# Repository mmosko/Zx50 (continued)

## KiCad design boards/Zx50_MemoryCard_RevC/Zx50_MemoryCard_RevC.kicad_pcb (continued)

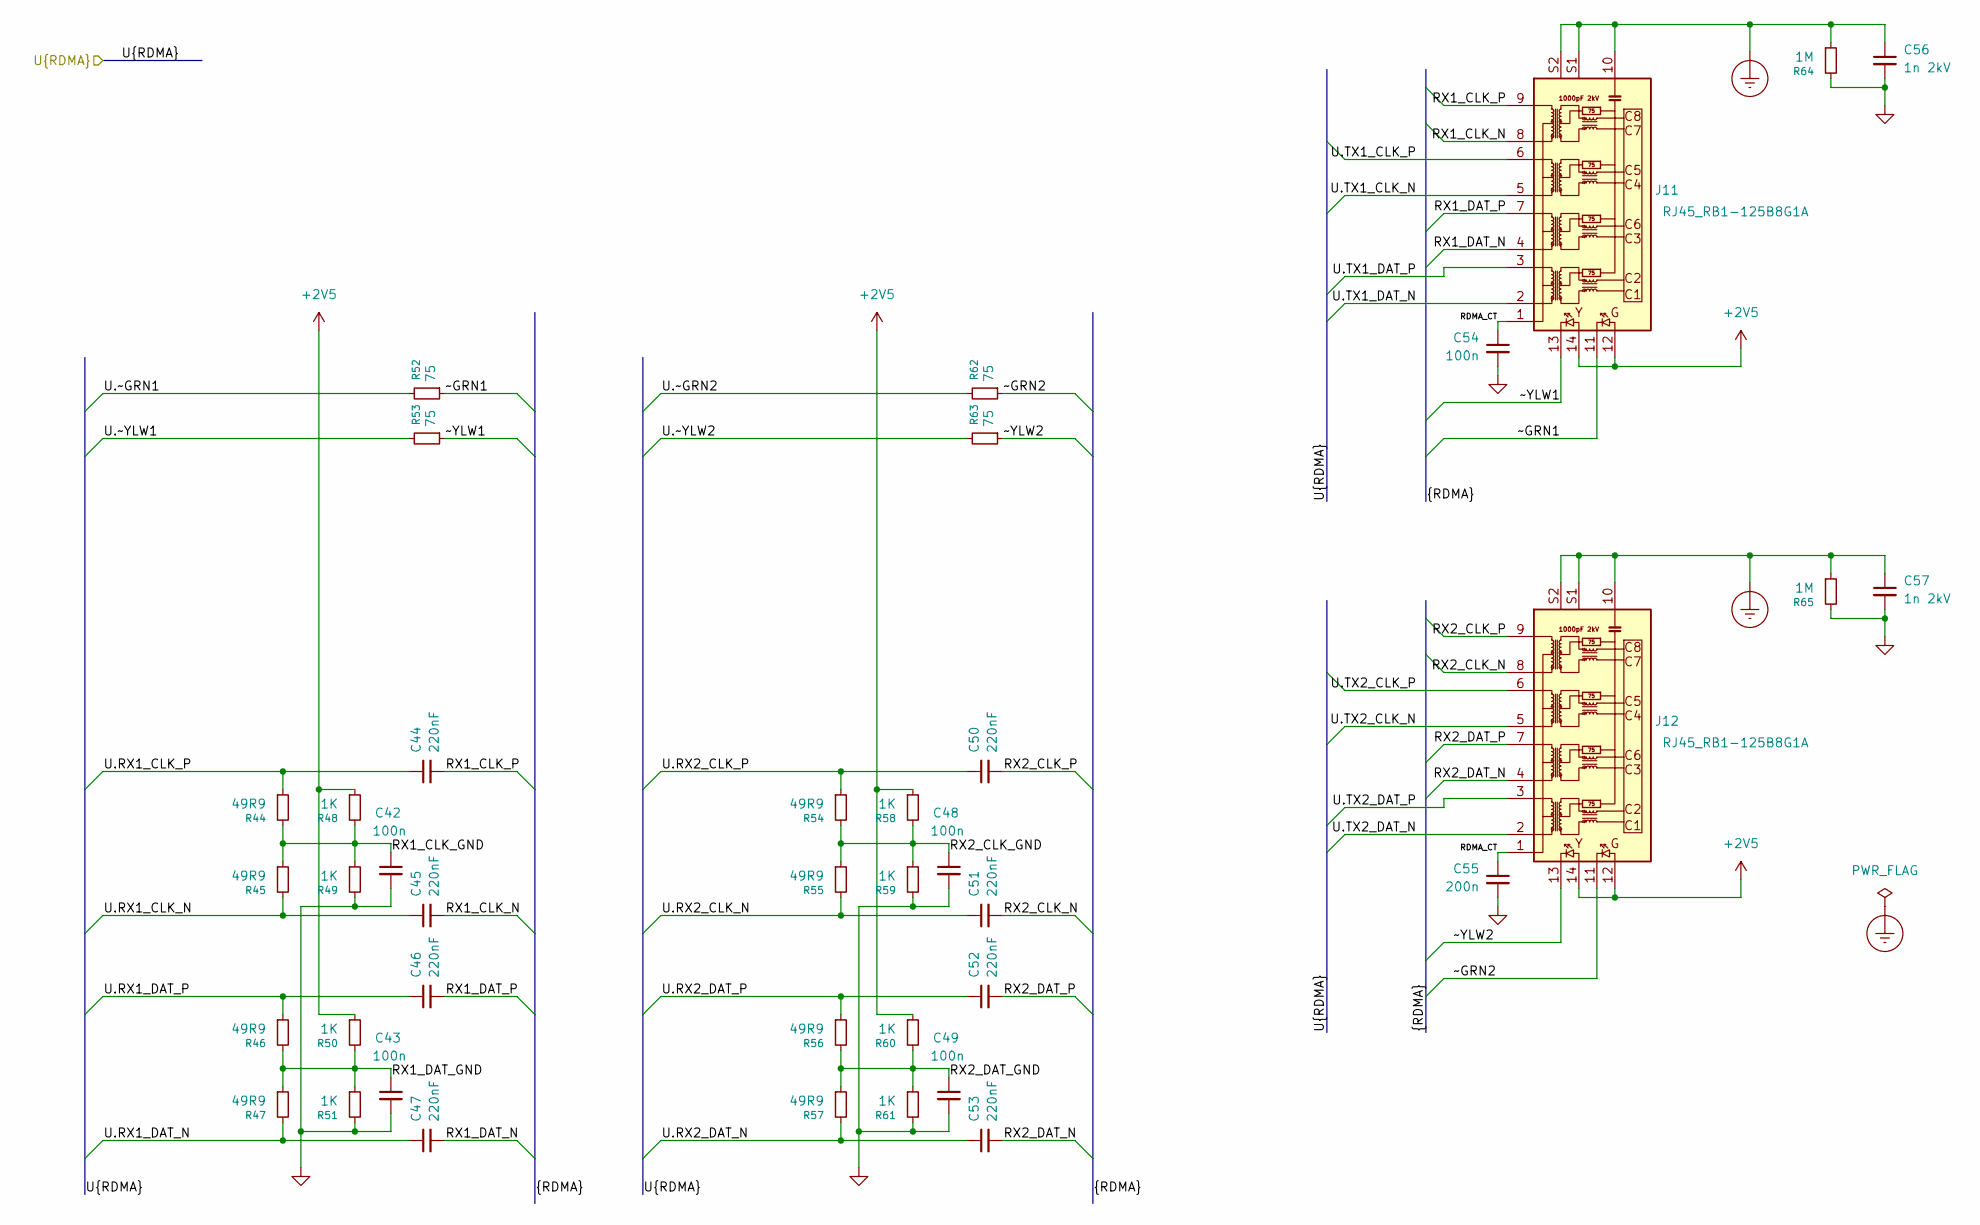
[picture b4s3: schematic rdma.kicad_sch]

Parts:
C42, C43, C48, C49, C54: 100n; C_0402_1005Metric; LCSC C1525
C44, C45, C46, C47, C50, C51, C52, C53: 220nF; C_0402_1005Metric; LCSC C16772
C55: 200n; C_0402_1005Metric; LCSC C1525
C56, C57: 1n 2kV; C_1206_3216Metric; LCSC C9196
J11, J12: RJ45_RB1-125B8G1A; HANRUN_HR911130A; MFG_PN HR911130C; LCSC C50933
R44, R45, R46, R47, R54, R55, R56, R57: 49R9; R_0402_1005Metric; MFG_PN 0402WGF499JTCE; LCSC C25120
R48, R49, R50, R51, R58, R59, R60, R61: 1K; R_0402_1005Metric; MFG_PN 0402WGF1001TCE; LCSC C11702
R52, R53, R62, R63: 75; R_0603_1608Metric; MFG_PN 0603WAF750JT5E; LCSC C4275
R64, R65: 1M; R_0805_2012Metric; MFG_PN 0805W8F1004T5E; LCSC C17514

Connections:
+2V5: J11.12, J11.14, J12.12, J12.14, R48.1, R50.1, R58.1, R60.1; also elsewhere on the board
/FPGA/RDMA/RDMA_CT: C54.1, C55.1, J11.1 (CT), J12.1 (CT)
/FPGA/RDMA/RX1_CLK_GND: C42.1, R44.2, R45.1, R48.2, R49.1
/FPGA/RDMA/RX1_CLK_N: C45.2, J11.8 (TD4+)
/FPGA/RDMA/RX1_CLK_P: C44.2, J11.9 (TD4-)
/FPGA/RDMA/RX1_DAT_GND: C43.1, R46.2, R47.1, R50.2, R51.1
/FPGA/RDMA/RX1_DAT_N: C47.2, J11.4 (TD2+)
/FPGA/RDMA/RX1_DAT_P: C46.2, J11.7 (TD2-)
/FPGA/RDMA/RX2_CLK_GND: C48.1, R54.2, R55.1, R58.2, R59.1
/FPGA/RDMA/RX2_CLK_N: C51.2, J12.8 (TD4+)
/FPGA/RDMA/RX2_CLK_P: C50.2, J12.9 (TD4-)
/FPGA/RDMA/RX2_DAT_GND: C49.1, R56.2, R57.1, R60.2, R61.1
/FPGA/RDMA/RX2_DAT_N: C53.2, J12.4 (TD2+)
/FPGA/RDMA/RX2_DAT_P: C52.2, J12.7 (TD2-)
/FPGA/RDMA/~GRN1: J11.11, R52.1
/FPGA/RDMA/~GRN2: J12.11, R62.1
/FPGA/RDMA/~YLW1: J11.13, R53.1
/FPGA/RDMA/~YLW2: J12.13, R63.1
/FPGA/U.RX1_CLK_N: C45.1, R45.2; also elsewhere on the board
/FPGA/U.RX1_CLK_P: C44.1, R44.1; also elsewhere on the board
/FPGA/U.RX1_DAT_N: C47.1, R47.2; also elsewhere on the board
/FPGA/U.RX1_DAT_P: C46.1, R46.1; also elsewhere on the board
/FPGA/U.RX2_CLK_N: C51.1, R55.2; also elsewhere on the board
/FPGA/U.RX2_CLK_P: C50.1, R54.1; also elsewhere on the board
/FPGA/U.RX2_DAT_N: C53.1, R57.2; also elsewhere on the board
/FPGA/U.RX2_DAT_P: C52.1, R56.1; also elsewhere on the board
/FPGA/U.TX1_CLK_N: J11.5 (TD3+); also elsewhere on the board
/FPGA/U.TX1_CLK_P: J11.6 (TD3-); also elsewhere on the board
/FPGA/U.TX1_DAT_N: J11.2 (TD1+); also elsewhere on the board
/FPGA/U.TX1_DAT_P: J11.3 (TD1-); also elsewhere on the board
/FPGA/U.TX2_CLK_N: J12.5 (TD3+); also elsewhere on the board
/FPGA/U.TX2_CLK_P: J12.6 (TD3-); also elsewhere on the board
/FPGA/U.TX2_DAT_N: J12.2 (TD1+); also elsewhere on the board
/FPGA/U.TX2_DAT_P: J12.3 (TD1-); also elsewhere on the board
/FPGA/U.~GRN1: R52.2; also elsewhere on the board
/FPGA/U.~GRN2: R62.2; also elsewhere on the board
/FPGA/U.~YLW1: R53.2; also elsewhere on the board
/FPGA/U.~YLW2: R63.2; also elsewhere on the board
Earth_Protective: C56.1, C57.1, J11.10 (GND), J11.S1, J11.S2, J12.10 (GND), J12.S1, J12.S2, R64.1, R65.1
GND: C42.2, C43.2, C48.2, C49.2, C54.2, C55.2, C56.2, C57.2, R49.2, R51.2, R59.2, R61.2, R64.2, R65.2; also elsewhere on the board

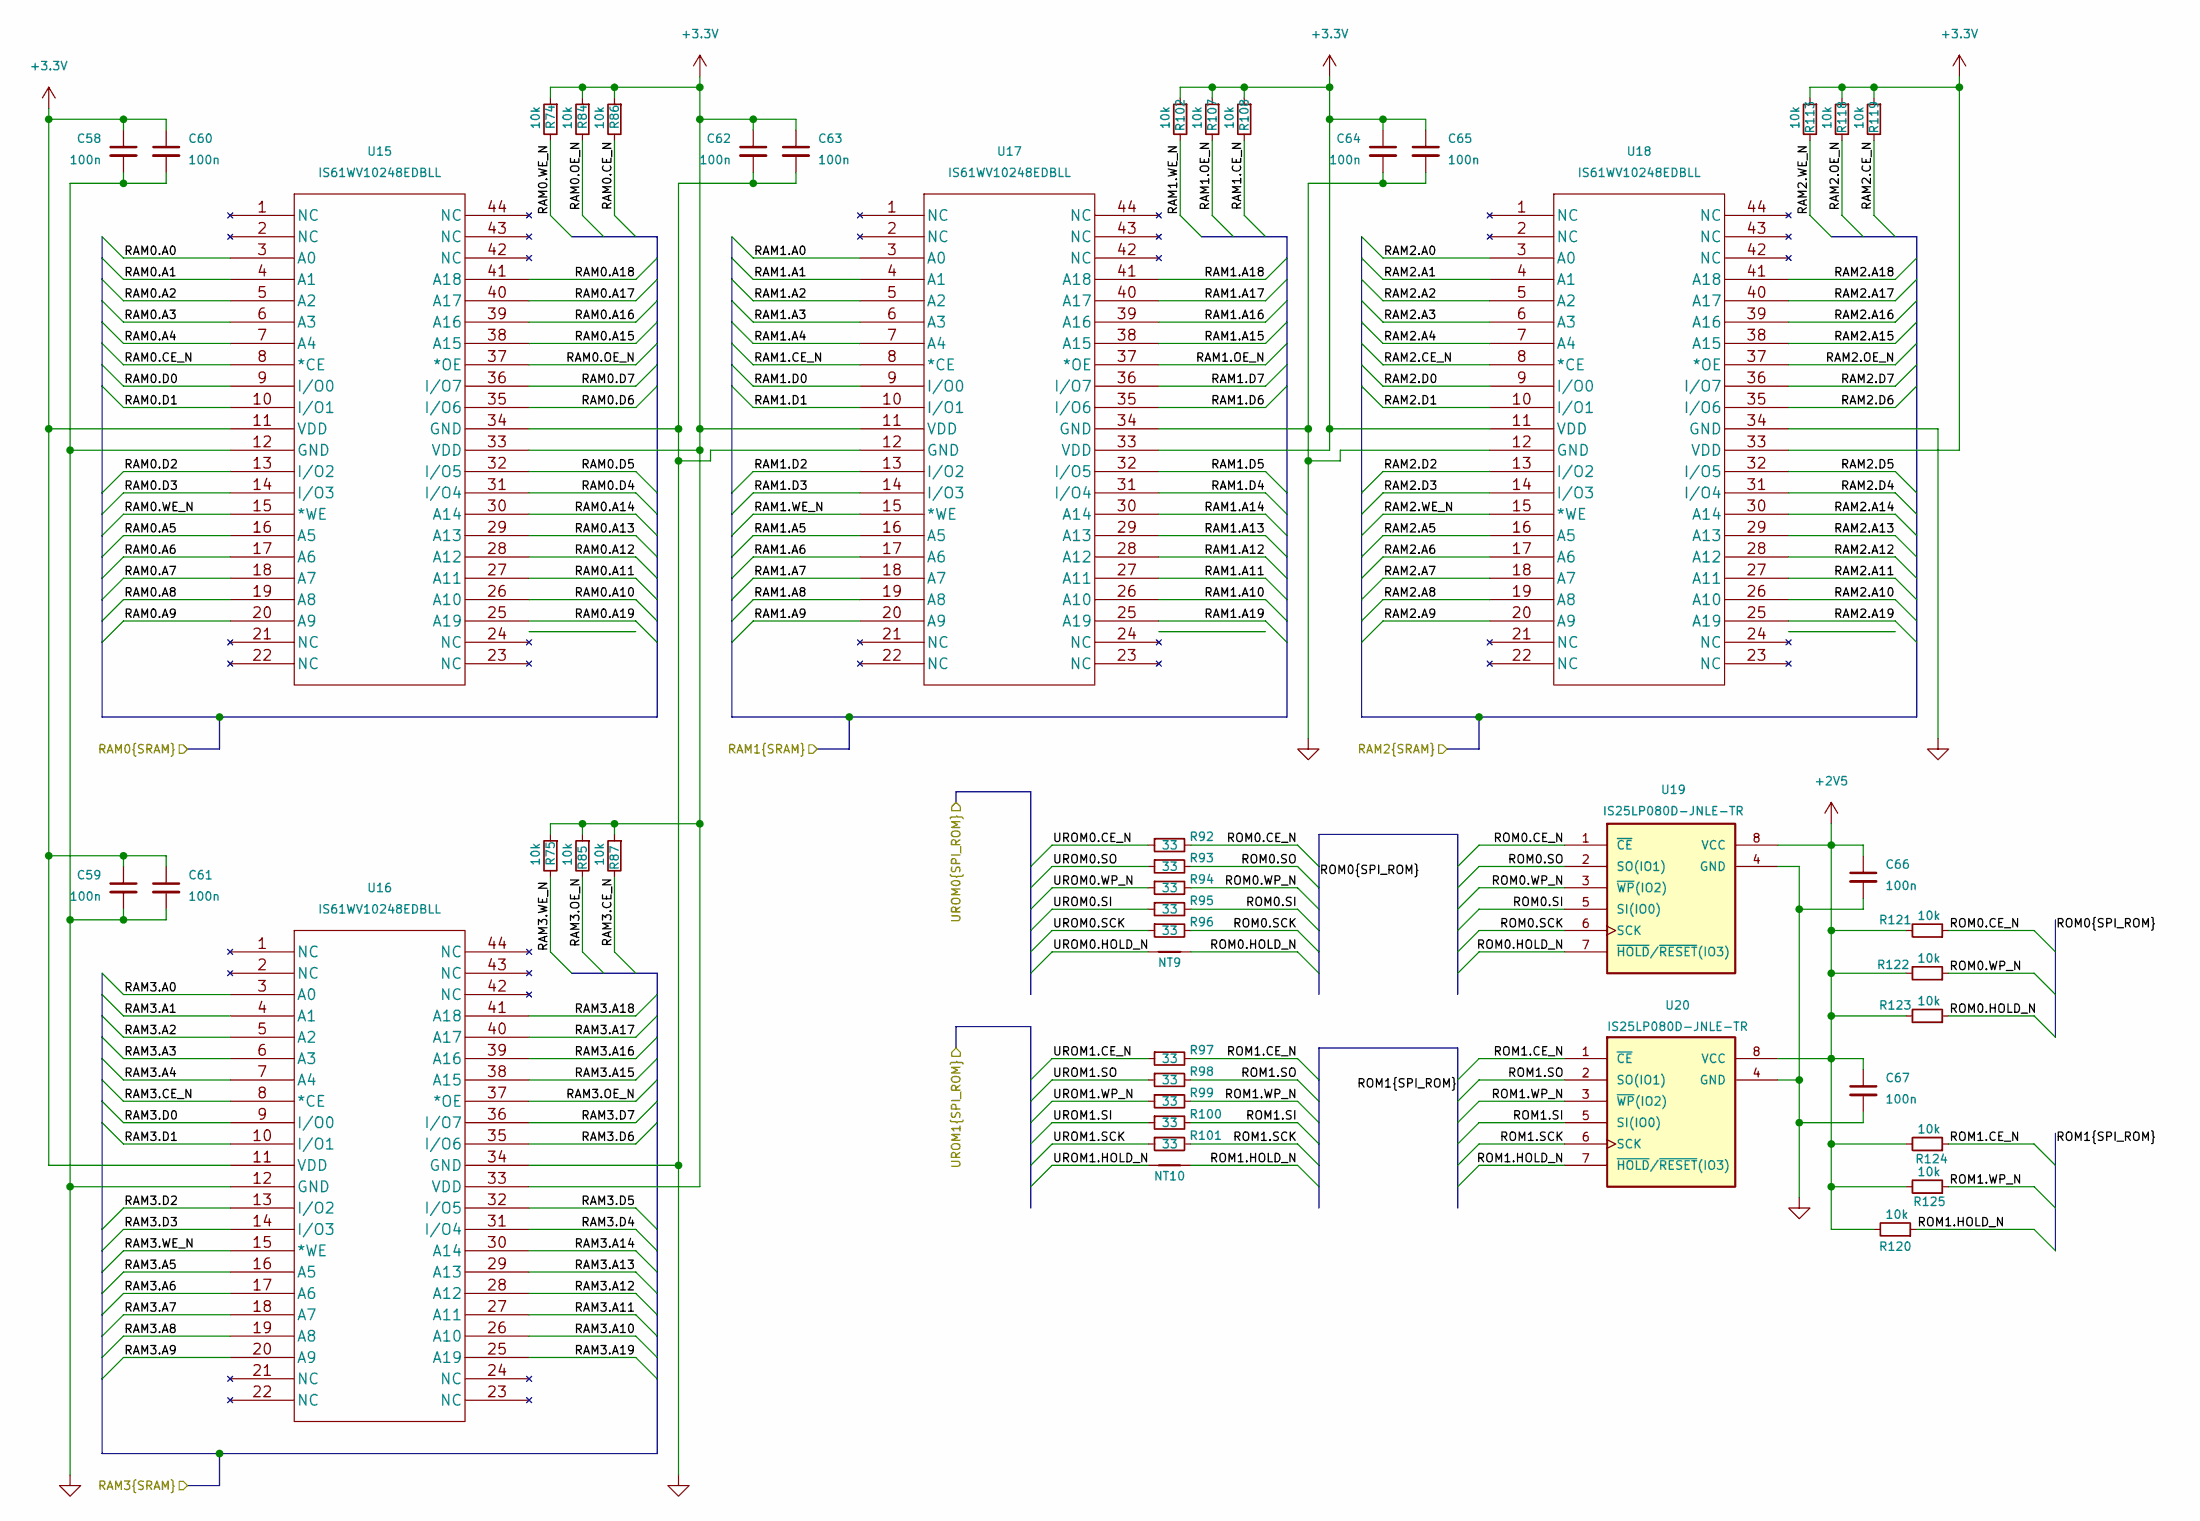
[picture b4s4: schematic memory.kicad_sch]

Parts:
C58, C59, C60, C61, C62, C63, C64, C65, C66, C67: 100n; C_0402_1005Metric; LCSC C1525
NT9, NT10: NetTie_2
R74, R75, R84, R85, R86, R87, R102, R107, R108, R113, R118, R119, R120, R121, R122, R123, R124, R125: 10k; R_0402_1005Metric; MFG_PN 0402WGF1002TCE; LCSC C25744
R92, R93, R94, R95, R96, R97, R98, R99, R100, R101: 33; R_0402_1005Metric; MFG_PN 0402WGF1000TCE; LCSC C25076
U15, U16, U17, U18: IS61WV10248EDBLL; TSOP-44_11P9X18P5_ISI; LCSC C1349228
U19, U20: IS25LP080D-JNLE-TR; SOIC127P600X88-8N; DigiKey_PN 706-1581-1-ND

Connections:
+2V5: C66.1, C67.1, R120.2, R121.2, R122.2, R123.2, R124.2, R125.2, U19.8 (VCC), U20.8 (VCC); also elsewhere on the board
+3.3V: C58.1, C59.1, C60.1, C61.1, C62.1, C63.1, C64.1, C65.1, R74.1, R75.1, R84.1, R85.1, R86.1, R87.1, R102.1, R107.1, R108.1, R113.1, R118.1, R119.1, U15.11 (VDD), U15.33 (VDD), U16.11 (VDD), U16.33 (VDD), U17.11 (VDD), U17.33 (VDD), U18.11 (VDD), U18.33 (VDD); also elsewhere on the board
/FPGA/RAM0.A0: U15.3 (A0)
/FPGA/RAM0.A1: U15.4 (A1)
/FPGA/RAM0.A2: U15.5 (A2)
/FPGA/RAM0.A3: U15.6 (A3)
/FPGA/RAM0.A4: U15.7 (A4)
/FPGA/RAM0.A5: U15.16 (A5)
/FPGA/RAM0.A6: U15.17 (A6)
/FPGA/RAM0.A7: U15.18 (A7)
/FPGA/RAM0.A8: U15.19 (A8)
/FPGA/RAM0.A9: U15.20 (A9)
/FPGA/RAM0.A10: U15.26 (A10)
/FPGA/RAM0.A11: U15.27 (A11)
/FPGA/RAM0.A12: U15.28 (A12)
/FPGA/RAM0.A13: U15.29 (A13)
/FPGA/RAM0.A14: U15.30 (A14)
/FPGA/RAM0.A15: U15.38 (A15)
/FPGA/RAM0.A16: U15.39 (A16)
/FPGA/RAM0.A17: U15.40 (A17)
/FPGA/RAM0.A18: U15.41 (A18)
/FPGA/RAM0.A19: U15.25 (A19)
/FPGA/RAM0.CE_N: R86.2, U15.8 (*CE)
/FPGA/RAM0.D0: U15.9 (I/O0)
/FPGA/RAM0.D1: U15.10 (I/O1)
/FPGA/RAM0.D2: U15.13 (I/O2)
/FPGA/RAM0.D3: U15.14 (I/O3)
/FPGA/RAM0.D4: U15.31 (I/O4)
/FPGA/RAM0.D5: U15.32 (I/O5)
/FPGA/RAM0.D6: U15.35 (I/O6)
/FPGA/RAM0.D7: U15.36 (I/O7)
/FPGA/RAM0.OE_N: R84.2, U15.37 (*OE)
/FPGA/RAM0.WE_N: R74.2, U15.15 (*WE)
/FPGA/RAM1.A0: U17.3 (A0); also elsewhere on the board
/FPGA/RAM1.A1: U17.4 (A1); also elsewhere on the board
/FPGA/RAM1.A2: U17.5 (A2); also elsewhere on the board
/FPGA/RAM1.A3: U17.6 (A3); also elsewhere on the board
/FPGA/RAM1.A4: U17.7 (A4); also elsewhere on the board
/FPGA/RAM1.A5: U17.16 (A5); also elsewhere on the board
/FPGA/RAM1.A6: U17.17 (A6); also elsewhere on the board
/FPGA/RAM1.A7: U17.18 (A7); also elsewhere on the board
/FPGA/RAM1.A8: U17.19 (A8); also elsewhere on the board
/FPGA/RAM1.A9: U17.20 (A9); also elsewhere on the board
/FPGA/RAM1.A10: U17.26 (A10); also elsewhere on the board
/FPGA/RAM1.A11: U17.27 (A11); also elsewhere on the board
/FPGA/RAM1.A12: U17.28 (A12); also elsewhere on the board
/FPGA/RAM1.A13: U17.29 (A13); also elsewhere on the board
/FPGA/RAM1.A14: U17.30 (A14); also elsewhere on the board
/FPGA/RAM1.A15: U17.38 (A15); also elsewhere on the board
/FPGA/RAM1.A16: U17.39 (A16); also elsewhere on the board
/FPGA/RAM1.A17: U17.40 (A17); also elsewhere on the board
/FPGA/RAM1.A18: U17.41 (A18); also elsewhere on the board
/FPGA/RAM1.A19: U17.25 (A19); also elsewhere on the board
/FPGA/RAM1.CE_N: R108.2, U17.8 (*CE); also elsewhere on the board
/FPGA/RAM1.D0: U17.9 (I/O0); also elsewhere on the board
/FPGA/RAM1.D1: U17.10 (I/O1); also elsewhere on the board
/FPGA/RAM1.D2: U17.13 (I/O2); also elsewhere on the board
/FPGA/RAM1.D3: U17.14 (I/O3); also elsewhere on the board
/FPGA/RAM1.D4: U17.31 (I/O4); also elsewhere on the board
/FPGA/RAM1.D5: U17.32 (I/O5); also elsewhere on the board
/FPGA/RAM1.D6: U17.35 (I/O6); also elsewhere on the board
/FPGA/RAM1.D7: U17.36 (I/O7); also elsewhere on the board
/FPGA/RAM1.OE_N: R107.2, U17.37 (*OE); also elsewhere on the board
/FPGA/RAM1.WE_N: R102.2, U17.15 (*WE); also elsewhere on the board
/FPGA/RAM2.A0: U18.3 (A0)
/FPGA/RAM2.A1: U18.4 (A1)
/FPGA/RAM2.A2: U18.5 (A2)
/FPGA/RAM2.A3: U18.6 (A3)
/FPGA/RAM2.A4: U18.7 (A4)
/FPGA/RAM2.A5: U18.16 (A5)
/FPGA/RAM2.A6: U18.17 (A6)
/FPGA/RAM2.A7: U18.18 (A7)
/FPGA/RAM2.A8: U18.19 (A8)
/FPGA/RAM2.A9: U18.20 (A9)
/FPGA/RAM2.A10: U18.26 (A10)
/FPGA/RAM2.A11: U18.27 (A11)
/FPGA/RAM2.A12: U18.28 (A12)
/FPGA/RAM2.A13: U18.29 (A13)
/FPGA/RAM2.A14: U18.30 (A14)
/FPGA/RAM2.A15: U18.38 (A15)
/FPGA/RAM2.A16: U18.39 (A16)
/FPGA/RAM2.A17: U18.40 (A17)
/FPGA/RAM2.A18: U18.41 (A18)
/FPGA/RAM2.A19: U18.25 (A19)
/FPGA/RAM2.CE_N: R119.2, U18.8 (*CE)
/FPGA/RAM2.D0: U18.9 (I/O0)
/FPGA/RAM2.D1: U18.10 (I/O1)
/FPGA/RAM2.D2: U18.13 (I/O2)
/FPGA/RAM2.D3: U18.14 (I/O3)
/FPGA/RAM2.D4: U18.31 (I/O4)
/FPGA/RAM2.D5: U18.32 (I/O5)
/FPGA/RAM2.D6: U18.35 (I/O6)
/FPGA/RAM2.D7: U18.36 (I/O7)
/FPGA/RAM2.OE_N: R118.2, U18.37 (*OE)
/FPGA/RAM2.WE_N: R113.2, U18.15 (*WE)
/FPGA/RAM3.A0: U16.3 (A0)
/FPGA/RAM3.A1: U16.4 (A1)
/FPGA/RAM3.A2: U16.5 (A2)
/FPGA/RAM3.A3: U16.6 (A3)
/FPGA/RAM3.A4: U16.7 (A4)
/FPGA/RAM3.A5: U16.16 (A5)
/FPGA/RAM3.A6: U16.17 (A6)
/FPGA/RAM3.A7: U16.18 (A7)
/FPGA/RAM3.A8: U16.19 (A8)
/FPGA/RAM3.A9: U16.20 (A9)
/FPGA/RAM3.A10: U16.26 (A10)
/FPGA/RAM3.A11: U16.27 (A11)
/FPGA/RAM3.A12: U16.28 (A12)
/FPGA/RAM3.A13: U16.29 (A13)
/FPGA/RAM3.A14: U16.30 (A14)
/FPGA/RAM3.A15: U16.38 (A15)
/FPGA/RAM3.A16: U16.39 (A16)
/FPGA/RAM3.A17: U16.40 (A17)
/FPGA/RAM3.A18: U16.41 (A18)
/FPGA/RAM3.A19: U16.25 (A19)
/FPGA/RAM3.CE_N: R87.2, U16.8 (*CE)
/FPGA/RAM3.D0: U16.9 (I/O0)
/FPGA/RAM3.D1: U16.10 (I/O1)
/FPGA/RAM3.D2: U16.13 (I/O2)
/FPGA/RAM3.D3: U16.14 (I/O3)
/FPGA/RAM3.D4: U16.31 (I/O4)
/FPGA/RAM3.D5: U16.32 (I/O5)
/FPGA/RAM3.D6: U16.35 (I/O6)
/FPGA/RAM3.D7: U16.36 (I/O7)
/FPGA/RAM3.OE_N: R85.2, U16.37 (*OE)
/FPGA/RAM3.WE_N: R75.2, U16.15 (*WE)
/FPGA/UROM0.CE_N: R92.1; also elsewhere on the board
/FPGA/UROM0.SCK: R96.1; also elsewhere on the board
/FPGA/UROM0.SI: R95.1; also elsewhere on the board
/FPGA/UROM0.SO: R93.1
/FPGA/UROM0.WP_N: R94.1; also elsewhere on the board
/FPGA/UROM1.CE_N: R97.1
/FPGA/UROM1.SCK: R101.1
/FPGA/UROM1.SI: R100.1
/FPGA/UROM1.SO: R98.1
/FPGA/UROM1.WP_N: R99.1
/FPGA/memory/ROM0.CE_N: R92.2, R121.1, U19.1 (~CE)
/FPGA/memory/ROM0.HOLD_N: NT9.2, R123.1, U19.7 (~HOLD/~RESET(IO3))
/FPGA/memory/ROM0.SCK: R96.2, U19.6 (SCK)
/FPGA/memory/ROM0.SI: R95.2, U19.5 (SI(IO0))
/FPGA/memory/ROM0.SO: R93.2, U19.2 (SO(IO1))
/FPGA/memory/ROM0.WP_N: R94.2, R122.1, U19.3 (~WP(IO2))
/FPGA/memory/ROM1.CE_N: R97.2, R124.1, U20.1 (~CE)
/FPGA/memory/ROM1.HOLD_N: NT10.2, R120.1, U20.7 (~HOLD/~RESET(IO3))
/FPGA/memory/ROM1.SCK: R101.2, U20.6 (SCK)
/FPGA/memory/ROM1.SI: R100.2, U20.5 (SI(IO0))
/FPGA/memory/ROM1.SO: R98.2, U20.2 (SO(IO1))
/FPGA/memory/ROM1.WP_N: R99.2, R125.1, U20.3 (~WP(IO2))
GND: C58.2, C59.2, C60.2, C61.2, C62.2, C63.2, C64.2, C65.2, C66.2, C67.2, U15.12 (GND), U15.34 (GND), U16.12 (GND), U16.34 (GND), U17.12 (GND), U17.34 (GND), U18.12 (GND), U18.34 (GND), U19.4 (GND), U20.4 (GND); also elsewhere on the board

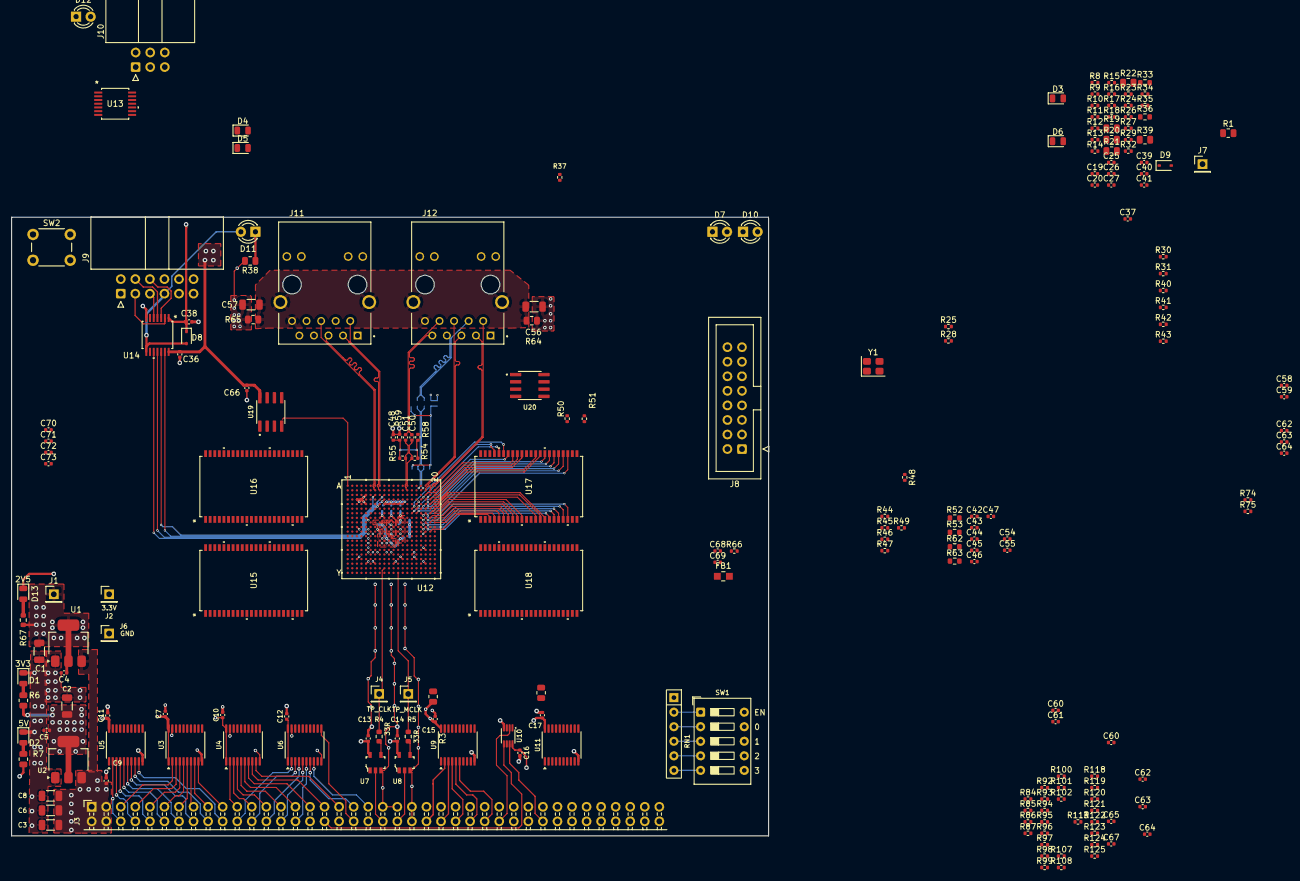
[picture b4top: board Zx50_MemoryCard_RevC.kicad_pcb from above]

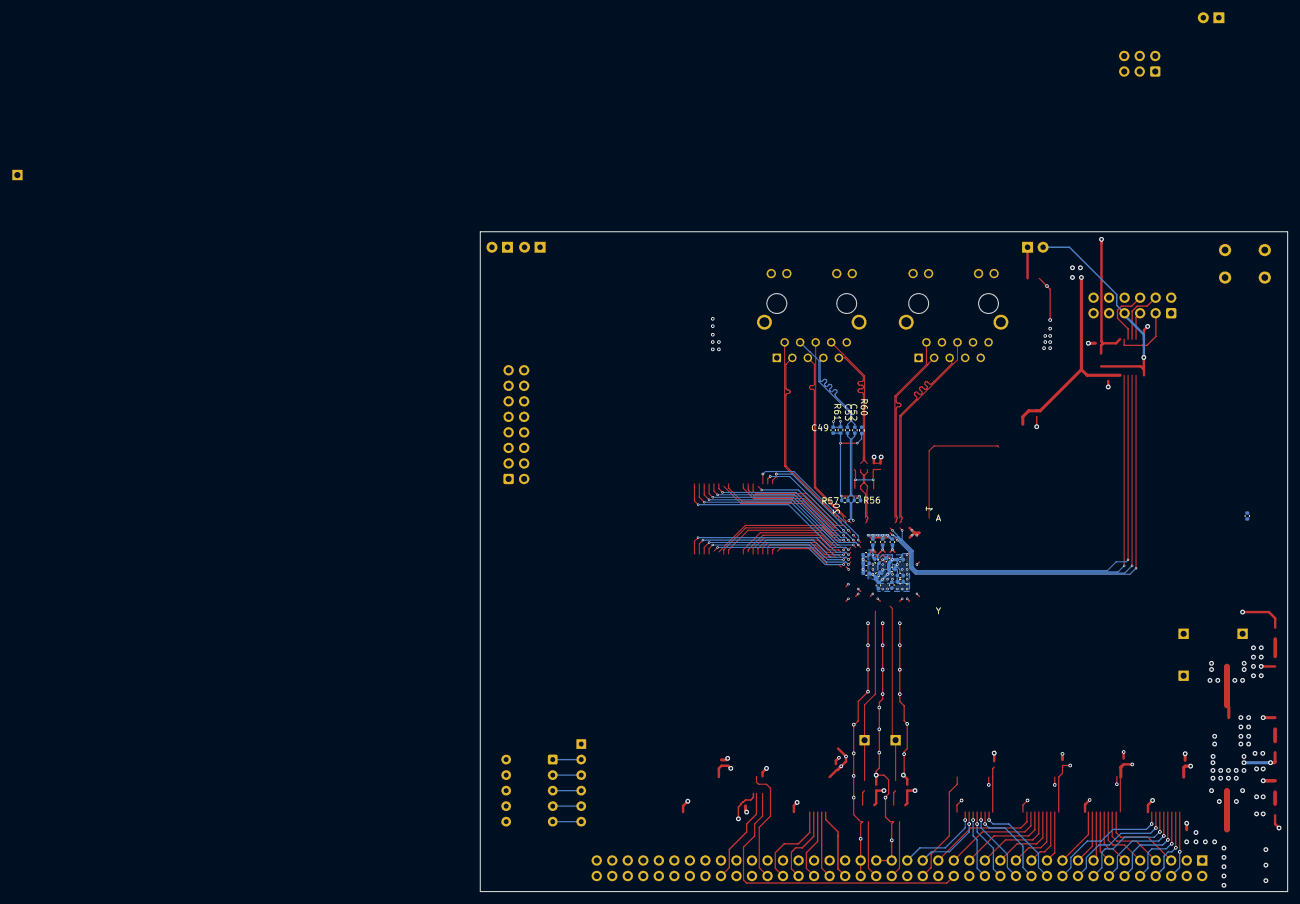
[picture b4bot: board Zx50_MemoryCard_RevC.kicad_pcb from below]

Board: 4 copper layers, 132.1 x 107.9 mm, 225 parts (23 on the bottom side), 209 nets.

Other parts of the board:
C60#2, C62#2, C63#2, C64#2: 100n; C_0402_1005Metric

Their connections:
+3.3V: C60#2.1, C62#2.1, C63#2.1, C64#2.1; also elsewhere on the board
GND: C60#2.2, C62#2.2, C63#2.2, C64#2.2; also elsewhere on the board

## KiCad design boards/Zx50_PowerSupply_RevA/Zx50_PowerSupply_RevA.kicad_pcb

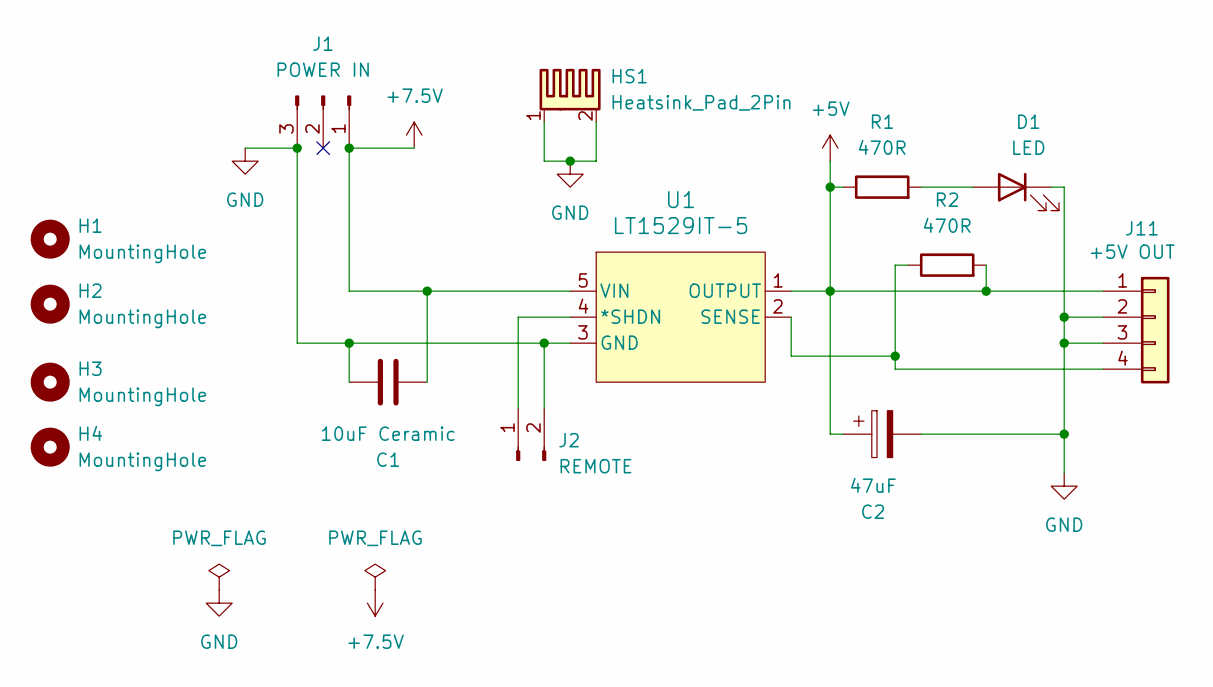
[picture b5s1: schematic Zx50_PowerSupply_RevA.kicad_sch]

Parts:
C1: 10uF Ceramic; CP_Radial_Tantal_D5.0mm_P2.50mm
C2: 47uF; CP_Radial_Tantal_D5.0mm_P2.50mm
D1: LED; LED_D3.0mm
H1, H2, H3, H4: MountingHole; MountingHole_3.2mm_M3; DigiKey_PN SJ5003-0-ND
HS1: Heatsink_Pad_2Pin; OMNI-UNI-PF-38
J1: POWER IN; PinHeader_1x03_P2.54mm_Vertical
J2: REMOTE; PinHeader_1x02_P1.00mm_Vertical
J11: +5V OUT; TerminalBlock_Phoenix_MKDS-1,5-4-5.08_1x04_P5.08mm_Horizont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; DigiKey_PN 277-1238-ND
R1, R2: 470R; R_Axial_DIN0207_L6.3mm_D2.5mm_P10.16mm_Horizontal
U1: LT1529IT-5; TO-220-5_P3.4x3.7mm_StaggerOdd_Lead3.8mm_Vertical; DigiKey_PN LT1529IT-5#PBF-ND

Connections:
+5V: C2.1, J11.1, R1.1, R2.2, U1.1 (OUTPUT)
+7.5V: C1.2, J1.1, U1.5 (VIN)
GND: C1.1, C2.2, D1.1 (K), HS1.1, HS1.2, J1.3, J2.2, J11.2, J11.3, U1.3 (GND)
unnamed: D1.2 (A), R1.2
unnamed: J2.1, U1.4 (*SHDN)
unnamed: J11.4, R2.1, U1.2 (SENSE)

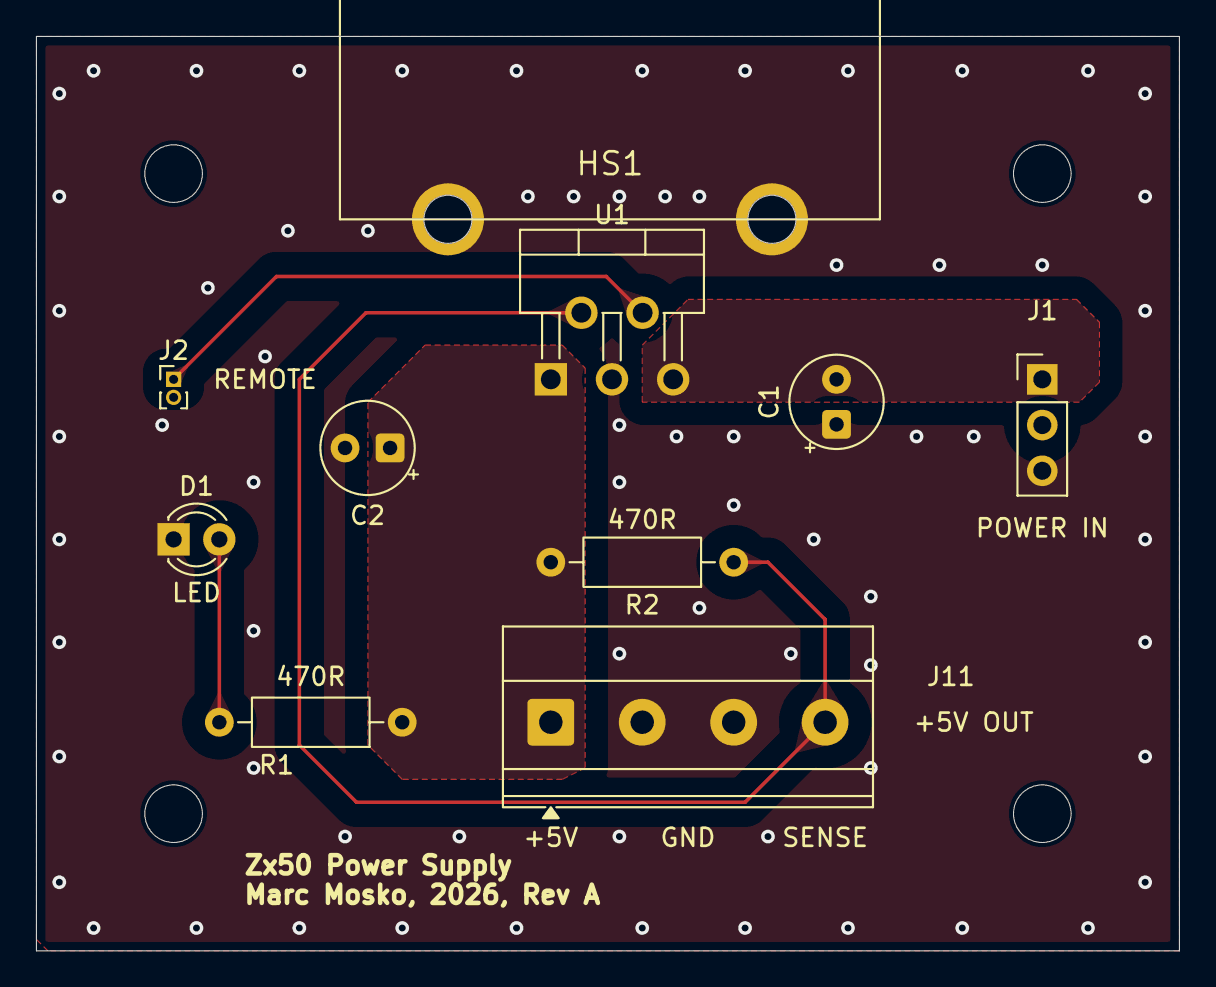
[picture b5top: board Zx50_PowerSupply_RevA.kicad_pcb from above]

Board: 2 copper layers, 63.5 x 50.8 mm, 14 parts (0 on the bottom side), 6 nets.

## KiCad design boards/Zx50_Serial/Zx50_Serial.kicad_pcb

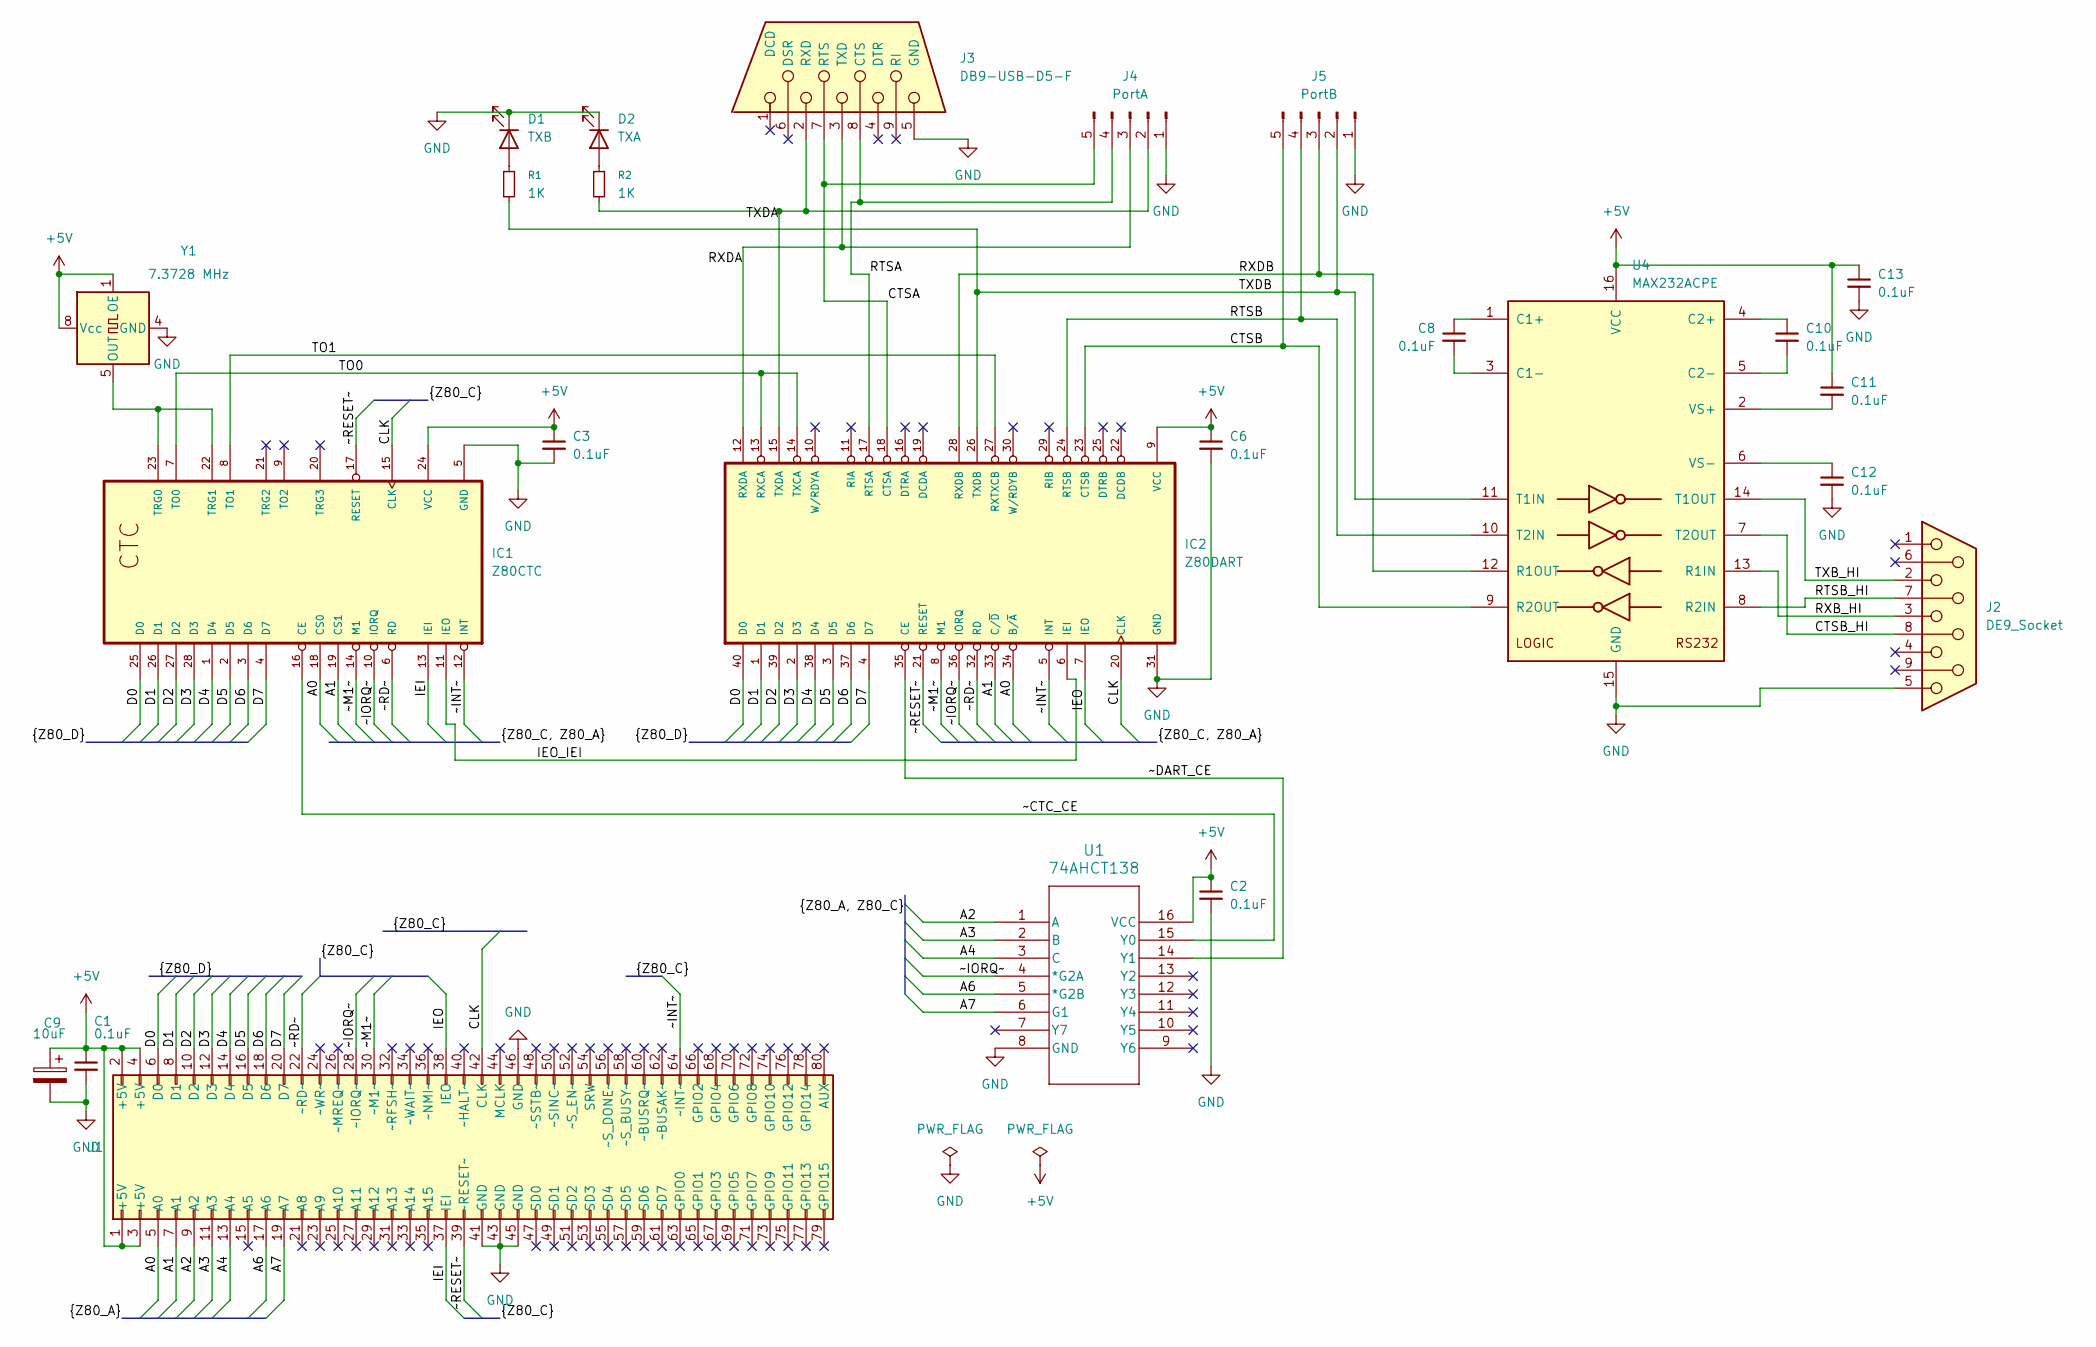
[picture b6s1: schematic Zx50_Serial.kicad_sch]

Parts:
C1, C2, C3, C6, C8, C10, C11, C12, C13: 0.1uF; C_Disc_D5.0mm_W2.5mm_P5.00mm; DigiKey_PN BC1101CT-ND
C9: 10uF; CP_Radial_Tantal_D5.0mm_P2.50mm; DigiKey_PN 399-1418-ND
D1: TXB; LED_D5.0mm
D2: TXA; LED_D5.0mm
IC1: Z80CTC; DIP-28_W7.62mm_Socket
IC2: Z80DART; DIP-40_W15.24mm_Socket
J1: Zx50_EdgeConnector; PinSocket_2x40_P2.54mm_Vertical_Oval; DigiKey_PN A34273-40-ND
J2: DE9_Socket; DSUB-9_Receptical_A-DF_09_A_KG-T2S
J3: DB9-USB-D5-F; DSUB-9_Receptical_A-DF_09_A_KG-T2S; DigiKey_PN 768-1108-ND
J4: PortA; PinHeader_1x05_P2.54mm_Horizontal
J5: PortB; PinHeader_1x05_P2.54mm_Horizontal
R1, R2: 1K; R_Axial_DIN0207_L6.3mm_D2.5mm_P10.16mm_Horizontal
U1: 74AHCT138; DIP-16_W7.62mm_Socket; DigiKey_PN 296-4666-5-ND
U4: MAX232ACPE; DIP-16_W7.62mm_Socket; DigiKey_PN MAX232ACPE+-ND
Y1: 7.3728 MHz; DIP-8_W7.62mm_Socket; DigiKey_PN 17-2485264-1-ND

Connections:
+5V: C1.1, C2.1, C3.1, C6.1, C9.1, C11.1, C13.1, IC1.24 (VCC), IC2.9 (VCC), J1.1 (+5V), J1.2 (+5V), J1.3 (+5V), J1.4 (+5V), U1.16 (VCC), U4.16 (VCC), Y1.1 (OE), Y1.8 (Vcc)
/A0: IC1.18 (CS0), IC2.34 (B/~A), J1.5 (A0)
/A1: IC1.19 (CS1), IC2.33 (C/~D), J1.7 (A1)
/A2: J1.9 (A2), U1.1 (A)
/A3: J1.11 (A3), U1.2 (B)
/A4: J1.13 (A4), U1.3 (C)
/A6: J1.17 (A6), U1.5 (*G2B)
/A7: J1.19 (A7), U1.6 (G1)
/CLK: IC1.15 (CLK), IC2.20 (CLK), J1.42 (CLK)
/CTSA: IC2.18 (CTSA), J3.7 (RTS), J4.5
/CTSB: IC2.23 (CTSB), J5.5, U4.9 (R2OUT)
/CTSB_HI: J2.8, U4.7 (T2OUT)
/D0: IC1.25 (D0), IC2.40 (D0), J1.6 (D0)
/D1: IC1.26 (D1), IC2.1 (D1), J1.8 (D1)
/D2: IC1.27 (D2), IC2.39 (D2), J1.10 (D2)
/D3: IC1.28 (D3), IC2.2 (D3), J1.12 (D3)
/D4: IC1.1 (D4), IC2.38 (D4), J1.14 (D4)
/D5: IC1.2 (D5), IC2.3 (D5), J1.16 (D5)
/D6: IC1.3 (D6), IC2.37 (D6), J1.18 (D6)
/D7: IC1.4 (D7), IC2.4 (D7), J1.20 (D7)
/IEI: IC1.13 (IEI), J1.37 (IEI)
/IEO: IC2.7 (IEO), J1.38 (IEO)
/IEO_IEI: IC1.11 (IEO), IC2.6 (IEI)
/RTSA: IC2.17 (RTSA), J3.8 (CTS), J4.4
/RTSB: IC2.24 (RTSB), J5.4, U4.10 (T2IN)
/RTSB_HI: J2.7, U4.8 (R2IN)
/RXB_HI: J2.3, U4.13 (R1IN)
/RXDA: IC2.12 (RXDA), J3.3 (TXD), J4.3
/RXDB: IC2.28 (RXDB), J5.3, U4.12 (R1OUT)
/TO0: IC1.7 (TO0), IC2.13 (RXCA), IC2.14 (TXCA)
/TO1: IC1.8 (TO1), IC2.27 (RXTXCB)
/TXB_HI: J2.2, U4.14 (T1OUT)
/TXDA: IC2.15 (TXDA), J3.2 (RXD), J4.2, R2.2
/TXDB: IC2.26 (TXDB), J5.2, R1.2, U4.11 (T1IN)
/~CTC_CE: IC1.16 (CE), U1.15 (Y0)
/~DART_CE: IC2.35 (CE), U1.14 (Y1)
/~INT~: IC1.12 (INT), IC2.5 (INT), J1.64 (~INT~)
/~IORQ~: IC1.10 (IORQ), IC2.36 (IORQ), J1.28 (~IORQ~), U1.4 (*G2A)
/~M1~: IC1.14 (M1), IC2.8 (M1), J1.30 (~M1~)
/~RD~: IC1.6 (RD), IC2.32 (RD), J1.22 (~RD~)
/~RESET~: IC1.17 (RESET), IC2.21 (RESET), J1.39 (~RESET~)
GND: C1.2, C2.2, C3.2, C6.2, C9.2, C12.2, C13.2, D1.1 (K), D2.1 (K), IC1.5 (GND), IC2.31 (GND), J1.41 (GND), J1.43 (GND), J1.45 (GND), J1.46 (GND), J2.5, J3.5 (GND), J4.1, J5.1, U1.8 (GND), U4.15 (GND), Y1.4 (GND)
unnamed: D1.2 (A), R1.1
unnamed: D2.2 (A), R2.1
unnamed: IC1.22 (TRG1), IC1.23 (TRG0), Y1.5 (OUT)
unnamed: C8.1, U4.1 (C1+)
unnamed: C8.2, U4.3 (C1-)
unnamed: C10.1, U4.4 (C2+)
unnamed: C10.2, U4.5 (C2-)
unnamed: C11.2, U4.2 (VS+)
unnamed: C12.1, U4.6 (VS-)

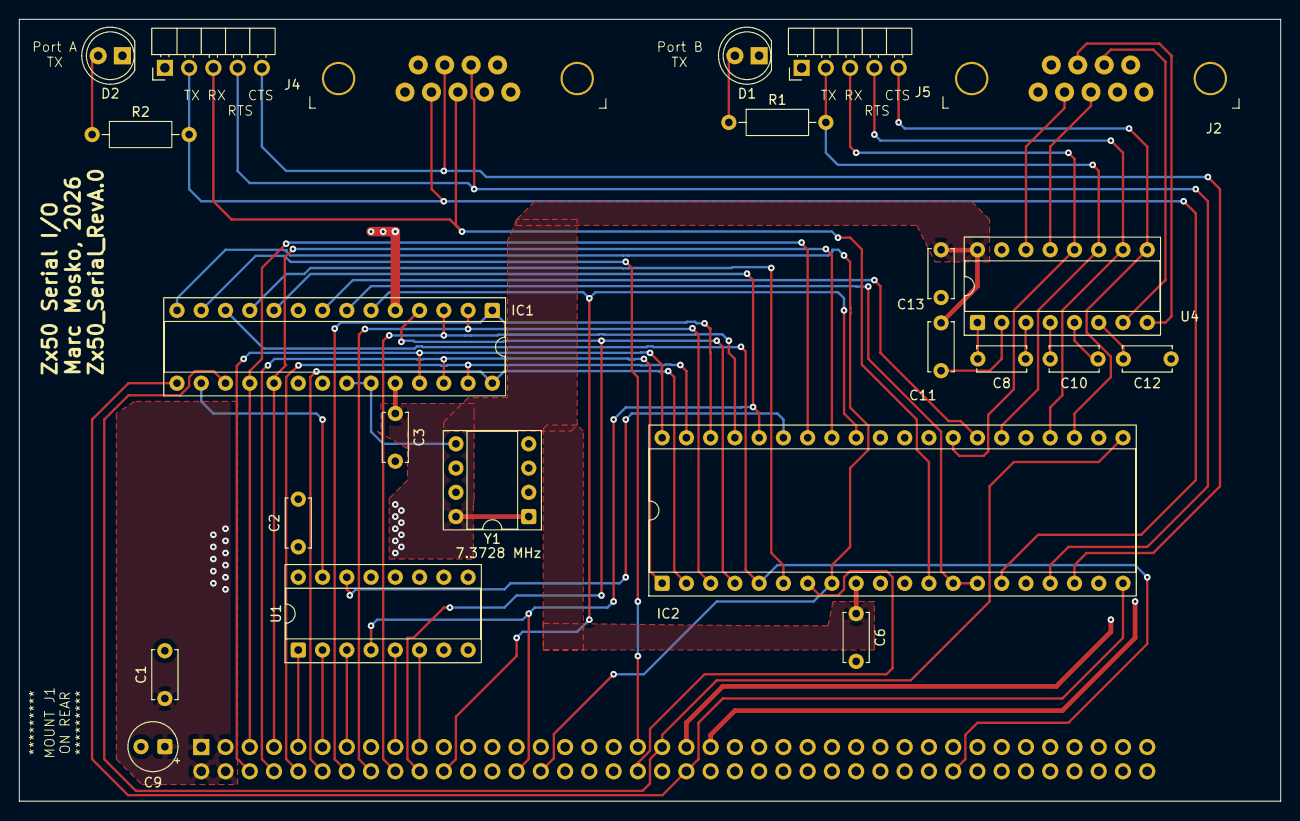
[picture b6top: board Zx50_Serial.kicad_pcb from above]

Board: 2 copper layers, 132.1 x 81.9 mm, 24 parts (1 on the bottom side), 51 nets.
